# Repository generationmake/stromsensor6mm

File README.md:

# stromsensor6mm
current sensor with TI INA226 and 6mm screw terminals

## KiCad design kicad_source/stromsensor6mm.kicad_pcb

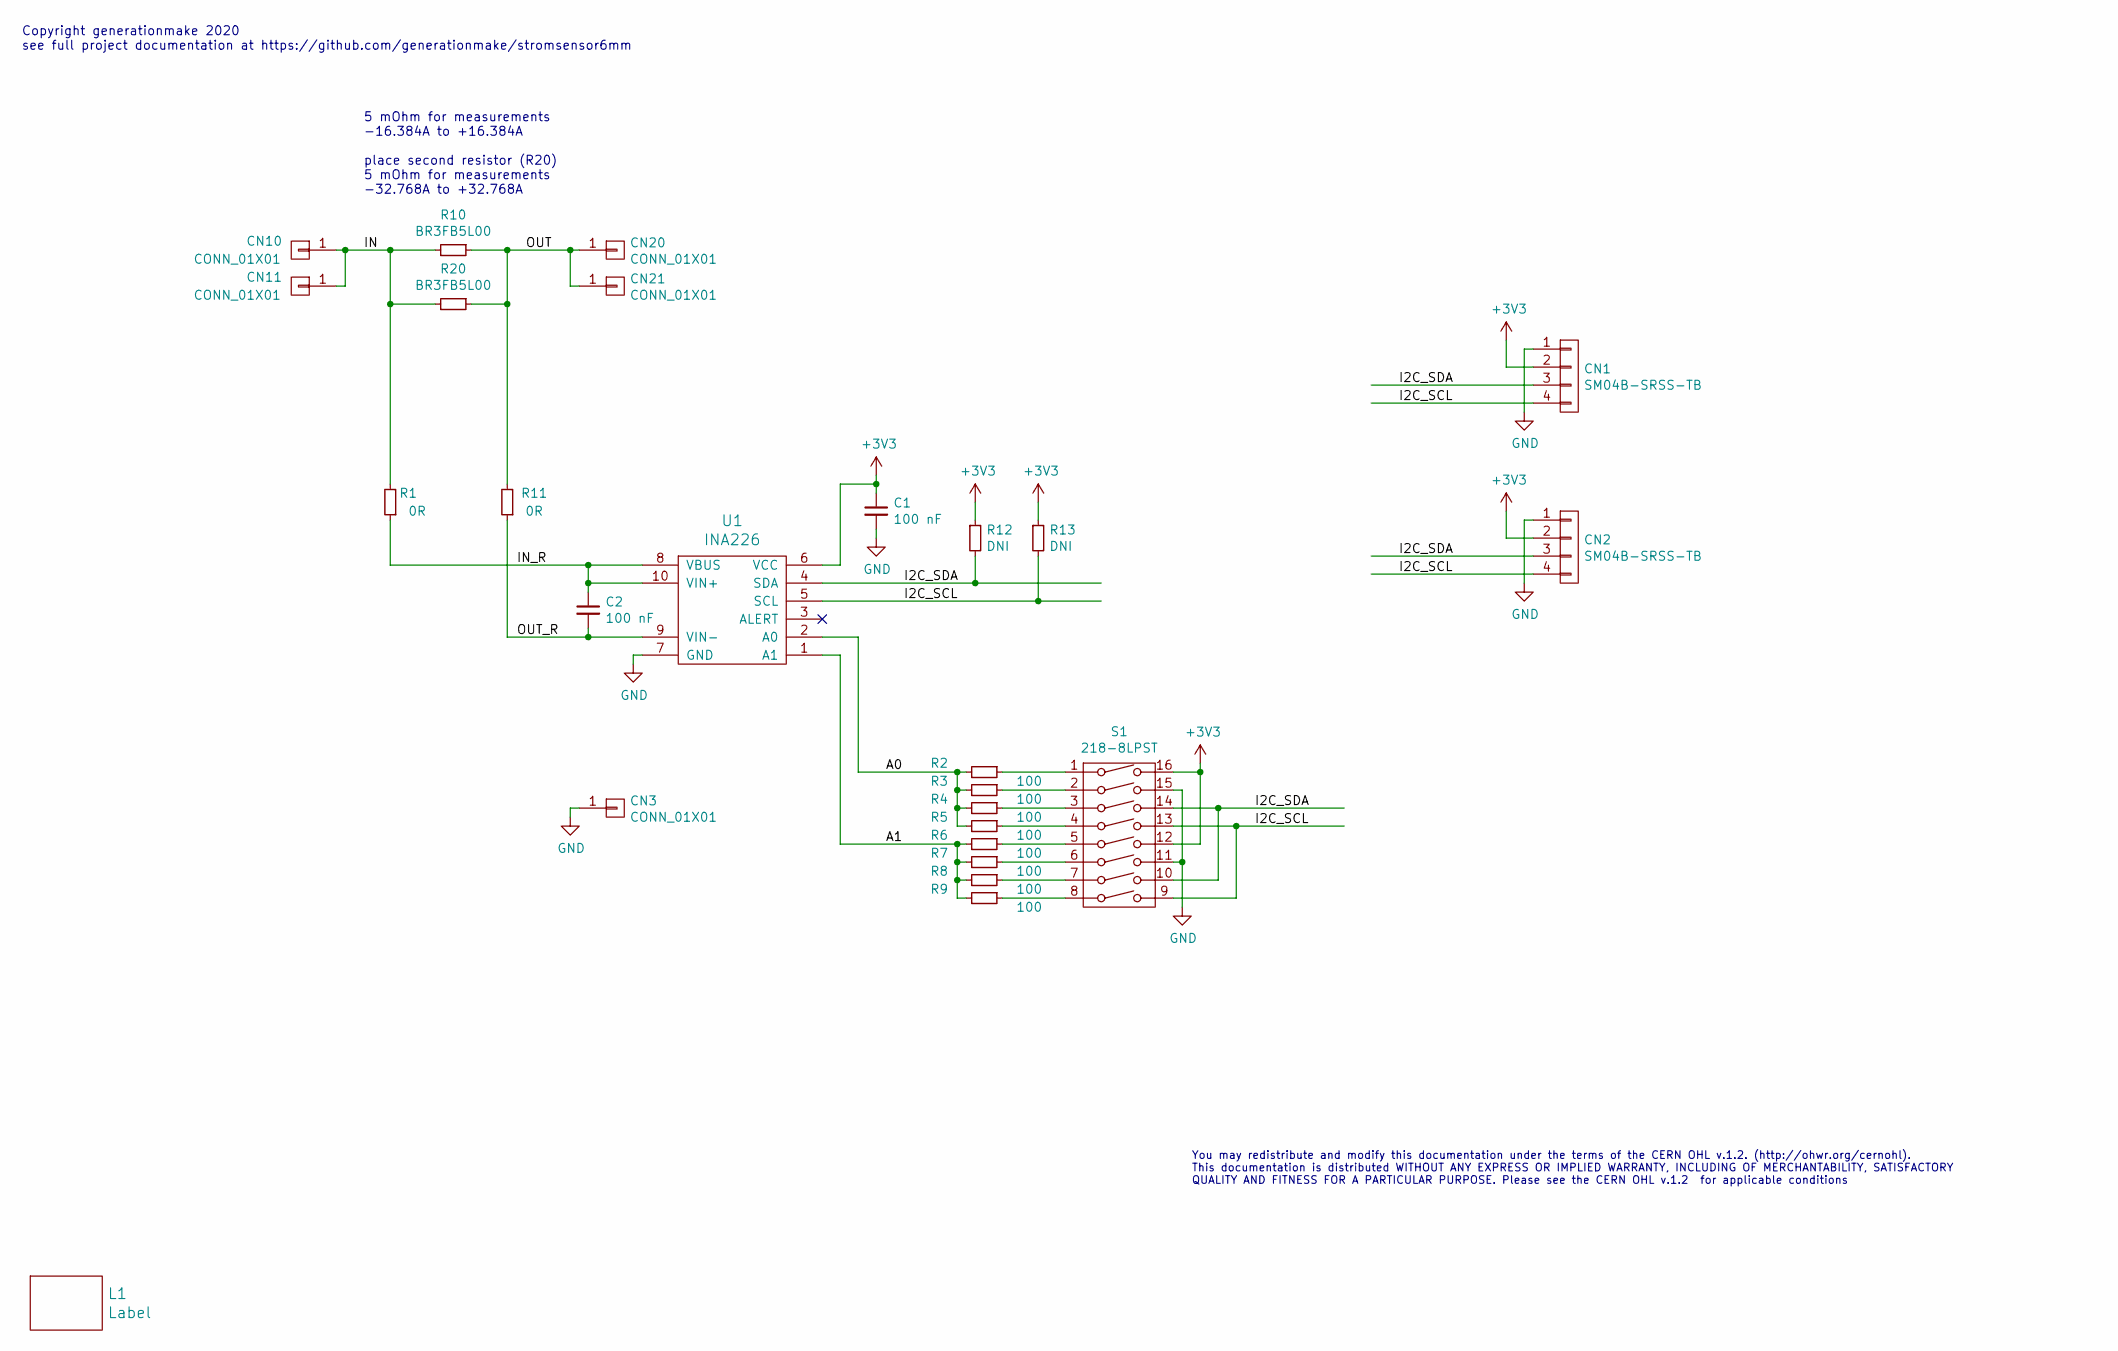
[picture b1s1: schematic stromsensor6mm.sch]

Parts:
C1, C2: 100 nF; C_0603
CN1, CN2: SM04B-SRSS-TB; Connectors_JST_SM04B-SRSS-TB
CN3, CN11, CN21: CONN_01X01; MHP_4.0_7.0
CN10, CN20: CONN_01X01; MHP_6.2_9.0
L1: Label; generationmake_small_silk
R1, R11: 0R; R_0603
R2, R3, R4, R5, R6, R7, R8, R9: 100; R_0603
R10, R20: BR3FB5L00; BR3
R12, R13: DNI; R_0603
S1: 218-8LPST; WE_416131160808
U1: INA226; MSOP-10_3x3mm_Pitch0.5mm

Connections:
+3V3: C1.1, CN1.2, CN2.2, R12.1, R13.1, S1.12, S1.16, U1.6 (VCC)
/A0: R2.2, R3.2, R4.2, R5.2, U1.2 (A0)
/A1: R6.2, R7.2, R8.2, R9.2, U1.1 (A1)
/I2C_SCL: CN1.4, CN2.4, R13.2, S1.9, S1.13, U1.5 (SCL)
/I2C_SDA: CN1.3, CN2.3, R12.2, S1.10, S1.14, U1.4 (SDA)
/IN: CN10.1, CN11.1, R1.2, R10.2, R20.2
/IN_R: C2.1, R1.1, U1.8 (VBUS), U1.10 (VIN+)
/OUT: CN20.1, CN21.1, R10.1, R11.2, R20.1
/OUT_R: C2.2, R11.1, U1.9 (VIN-)
GND: C1.2, CN1.1, CN2.1, CN3.1, S1.11, S1.15, U1.7 (GND)
unnamed: R2.1, S1.1
unnamed: R3.1, S1.2
unnamed: R4.1, S1.3
unnamed: R5.1, S1.4
unnamed: R6.1, S1.5
unnamed: R7.1, S1.6
unnamed: R8.1, S1.7
unnamed: R9.1, S1.8

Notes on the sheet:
5 mOhm for measurements -16.384A to +16.384A place second resistor (R20) 5 mOhm for measurements -32.768A to +32.768A
Copyright generationmake 2020 see full project documentation at https://github.com/generationmake/stromsensor6mm
You may redistribute and modify this documentation under the terms of the CERN OHL v.1.2. (http://ohwr.org/cernohl). This documentation is distributed WITHOUT ANY EXPRESS OR IMPLIED WARRANTY, INCLUDING OF MERCHANTABILITY, SATISFACTORY QUALITY AND FITNESS FOR A PARTICULAR PURPOSE. Please see the CER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

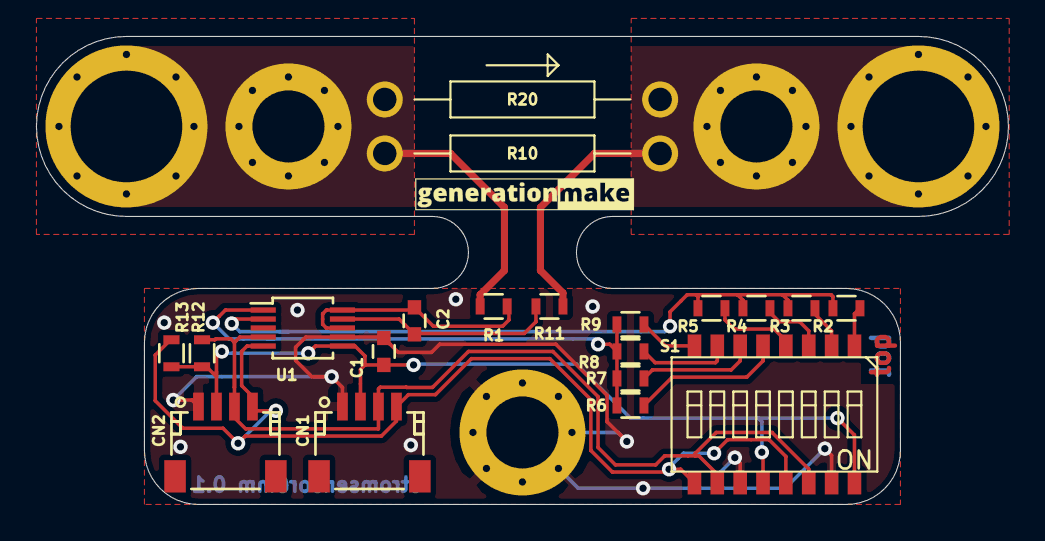
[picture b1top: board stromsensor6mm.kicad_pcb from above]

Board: 2 copper layers, 54.0 x 26.0 mm, 26 parts (0 on the bottom side), 18 nets.

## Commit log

2020-07-29 added kicad project with schematic and layout
2020-07-29 changed mounting holes for connection to wires
2020-07-29 changed current sensor to more robust part
2020-07-29 changed dip switch, updated placement and pcb shape
2020-07-29 updated layout, added decoupling capacitor on current sense
2020-07-30 finished layout
2020-07-30 added rendering
2020-08-30 current sensor input filtering works not as intended, changed R1 and R11 to 0 Ohm
2020-08-30 added description and documentation in schematic and layout, added pdfs
2020-08-30 added license information
2020-08-30 added step file
2020-09-13 added Arduino example with two stromsensor6mm boards
2020-09-13 added readme for arduino exmaples

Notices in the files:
kicad_source/stromsensor6mm.kicad_pcb:
This documentation describes Open Hardware and is licensed
under the CERN OHL v. 1.2.
kicad_source/stromsensor6mm.sch:
This documentation describes Open Hardware and is licensed under the CERN OHL v. 1.2.
